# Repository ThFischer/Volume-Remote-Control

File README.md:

# Volume Remote Control

This project contains a hard- and software solution to control the volume, balance and muting of a stereo line signal.

## Motivation
I was not able to control the volume of my home cinema setup remotely, because I use a Logitech Z4 which has only a wired volume remote:
```
         Fire TV Stick
              ▼
HDMI to HDMI and Audio Converter
    ┌─────────┴────────────┐
    ▼                      ▼
Video Projector       2.1 Speaker System
                        (Logitech Z4)
```
## Hardware

The main components are a microcontroller ([ATmega328P](https://www.microchip.com/wwwproducts/en/ATmega328P)) and a electronic volume controller IC ([PT2257](https://dtsheet.com/doc/592434/ptc-pt2257-s)). You can find the KiCad files (schema and PCB) in the [hardware directory](./hardware/). I used a single layer PCB which I made via [direct toner transfer method](https://www.electronicshub.org/how-to-make-pcb-at-home/). The shape of the PCB fits exactly into a [TerraTec CINERGY T2 case](https://commons.wikimedia.org/wiki/File:TerraTec_Cinergy_T%C2%B2-92062.jpg). The Volume Remote Control is connected between the audio output of the HDMI Converter and audio input of the 2.1 Speaker System.

## Software
I used [Visual Studio Code](https://code.visualstudio.com/download) and the [PlatformIO extension](https://platformio.org/install/ide?install=vscode). You can find the PlatformIO project files in the [software directory](./software/). Thanks to ["IRMP - Infrared Multi Protocol Decoder + Encoder"](https://github.com/ukw100/IRMP) library it provides support for thousands of IR Remotes (I use a [Apple Remote 2nd Gen.](https://en.wikipedia.org/wiki/Apple_Remote)).

## Flashing the Firmware
I used an Arduino UNO to flash the ATmega328P via the ISP connector on the PCB. For more details see [ArduinoISP](https://www.arduino.cc/en/pmwiki.php?n=Tutorial/ArduinoISP)

## Handling

### "Learn a new remote" mode
The start of this mode is indicated by alternate green and red flashing LED until the first button is learned.

When the Controller is powered on without having learned successfully a remote before, it starts automatically in this mode. You can also enter this mode after a remote was already learned by power of and on the controller and press a button on the remote within the first 5 seconds (green LED is on).
Important: To prevent unintended re-learning (e.g. your remote stuck in the couch and a button is pressed permanently) a pressed button is ignored if this button and the first button to learn (Volume up) is the same!

It expects the learning of remote buttons in this order:

1. Volume up
1. Volume down
1. Mute on/off
1. Balance left
1. Balance right
1. Preset

Each successful learned button is confirmed by flashing the green LED for 1 second. If an invalid IR command was received (e.g. from a second remote which has a different address) the learning mode will be interrupted.
In case you don't want define all buttons (e.g. your remote has less buttons) you can press a button which was already assigned. In this case the function will be not supported.

If the last button is learned, the green LED flashes 3 times and the new learned buttons are stored into the non volatile memory of the µC. 

### Volume
Press the learned "Volume up" or "Volume down" button to increase or decrease the volume.

### Balance
Press the learned "Balance left" or "Balance right" button to shift the balance to the left or right.

### Mute
Press the learned "Mute" button to toggle mute on and off.

### Preset
To restore the presets for volume and balance press and release the learned "Preset" button.
To store the current volume and balance as presets press and hold the learned "Preset" button for 3 seconds.

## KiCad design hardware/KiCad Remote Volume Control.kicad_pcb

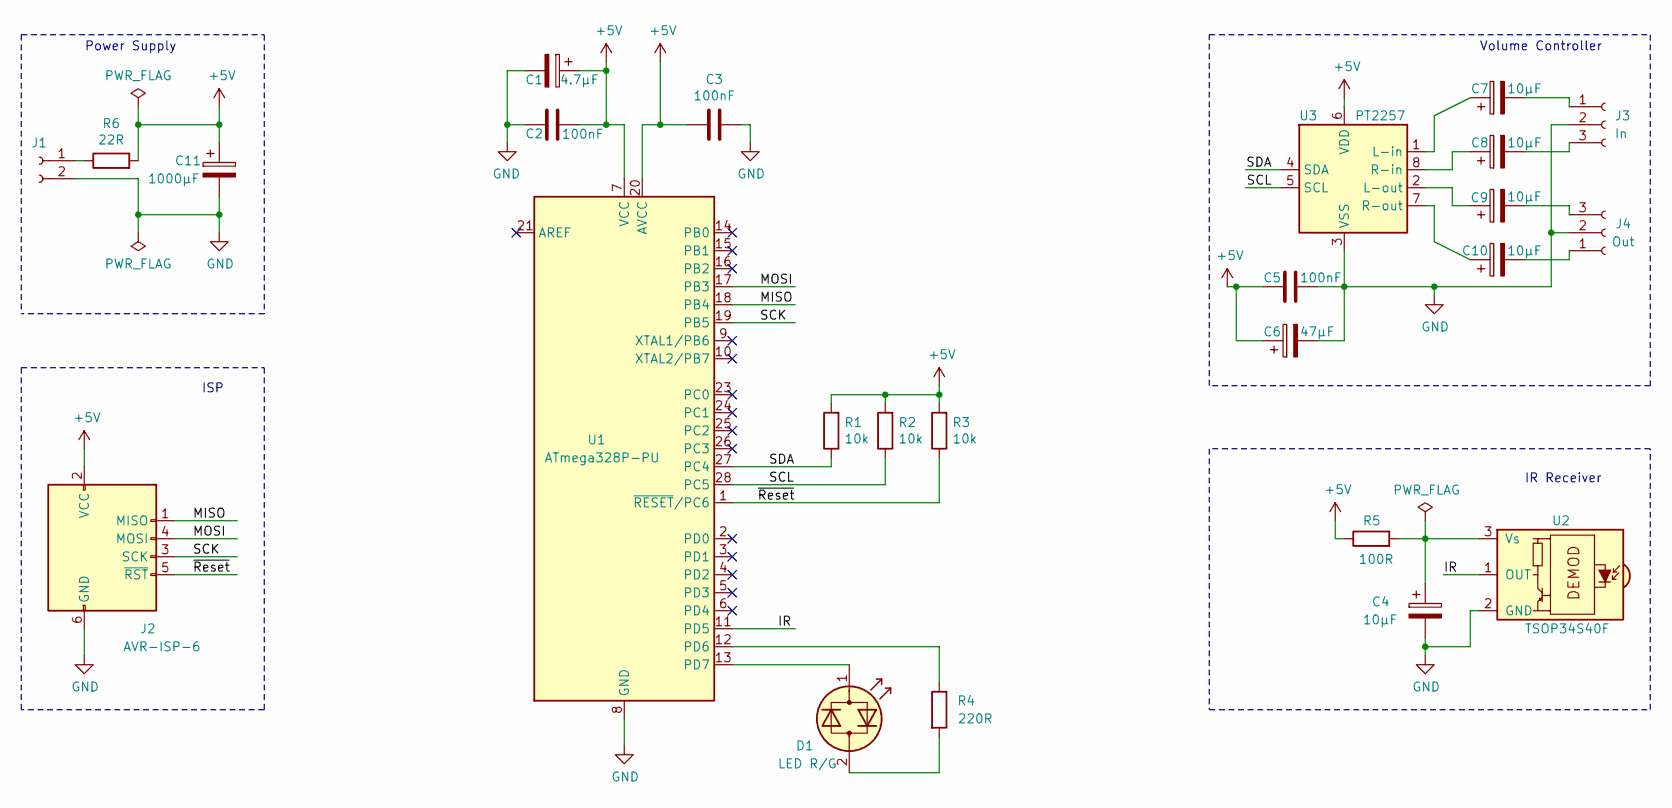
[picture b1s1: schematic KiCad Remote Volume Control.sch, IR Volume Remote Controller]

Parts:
C1: 4.7µF; CP_Radial_D4.0mm_P1.50mm
C2, C3, C5: 100nF; C_Disc_D3.0mm_W2.0mm_P2.50mm
C4, C7, C8, C9, C10: 10µF; CP_Radial_D4.0mm_P1.50mm
C6: 47µF; CP_Radial_D4.0mm_P1.50mm
C11: 1000µF; CP_Radial_D10.0mm_P5.00mm
D1: LED R/G; LED_D3.0mm
J1: Conn_01x02_Female; JST_XH_B2B-XH-A_1x02_P2.50mm_Vertical
J2: AVR-ISP-6; PinHeader_2x03_P2.54mm_Vertical
J3: In; PinHeader_1x03_P2.54mm_Vertical
J4: Out; PinHeader_1x03_P2.54mm_Vertical
R1, R2, R3: 10k; R_Axial_DIN0207_L6.3mm_D2.5mm_P2.54mm_Vertical
R4: 220R; R_Axial_DIN0207_L6.3mm_D2.5mm_P2.54mm_Vertical
R5: 100R; R_Axial_DIN0207_L6.3mm_D2.5mm_P2.54mm_Vertical
R6: 22R; R_Axial_DIN0207_L6.3mm_D2.5mm_P2.54mm_Vertical
U1: ATmega328P-PU; DIP-28_W7.62mm
U2: TSOP34S40F; Vishay_MOLD-3Pin
U3: PT2257; DIP-8_W7.62mm

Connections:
+5V: C1.1, C2.1, C3.1, C5.1, C6.1, C11.1, J2.2 (VCC), R1.2, R2.2, R3.2, R5.1, R6.2, U1.7 (VCC), U1.20 (AVCC), U3.6 (VDD)
/IR: U1.11 (PD5), U2.1 (OUT)
/MISO: J2.1 (MISO), U1.18 (PB4)
/MOSI: J2.4 (MOSI), U1.17 (PB3)
/SCK: J2.3 (SCK), U1.19 (PB5)
/SCL: R2.1, U1.28 (PC5), U3.5 (SCL)
/SDA: R1.1, U1.27 (PC4), U3.4 (SDA)
/~Reset: J2.5 (~RST), R3.1, U1.1 (~RESET~/PC6)
GND: C1.2, C2.2, C3.2, C4.2, C5.2, C6.2, C11.2, J1.2, J2.6 (GND), J3.2, J4.2, U1.8 (GND), U1.22 (GND), U2.2 (GND), U3.3 (VSS)
unnamed: C4.1, R5.2, U2.3 (Vs)
unnamed: C7.1, U3.1 (L-in)
unnamed: C7.2, J3.1
unnamed: C8.1, U3.8 (R-in)
unnamed: C8.2, J3.3
unnamed: C9.1, U3.2 (L-out)
unnamed: C9.2, J4.3
unnamed: C10.1, U3.7 (R-out)
unnamed: C10.2, J4.1
unnamed: D1.1 (KA), U1.13 (PD7)
unnamed: D1.2 (AK), R4.2
unnamed: J1.1, R6.1
unnamed: R4.1, U1.12 (PD6)

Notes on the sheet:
Power Supply
ISP
IR Receiver
Volume Controller

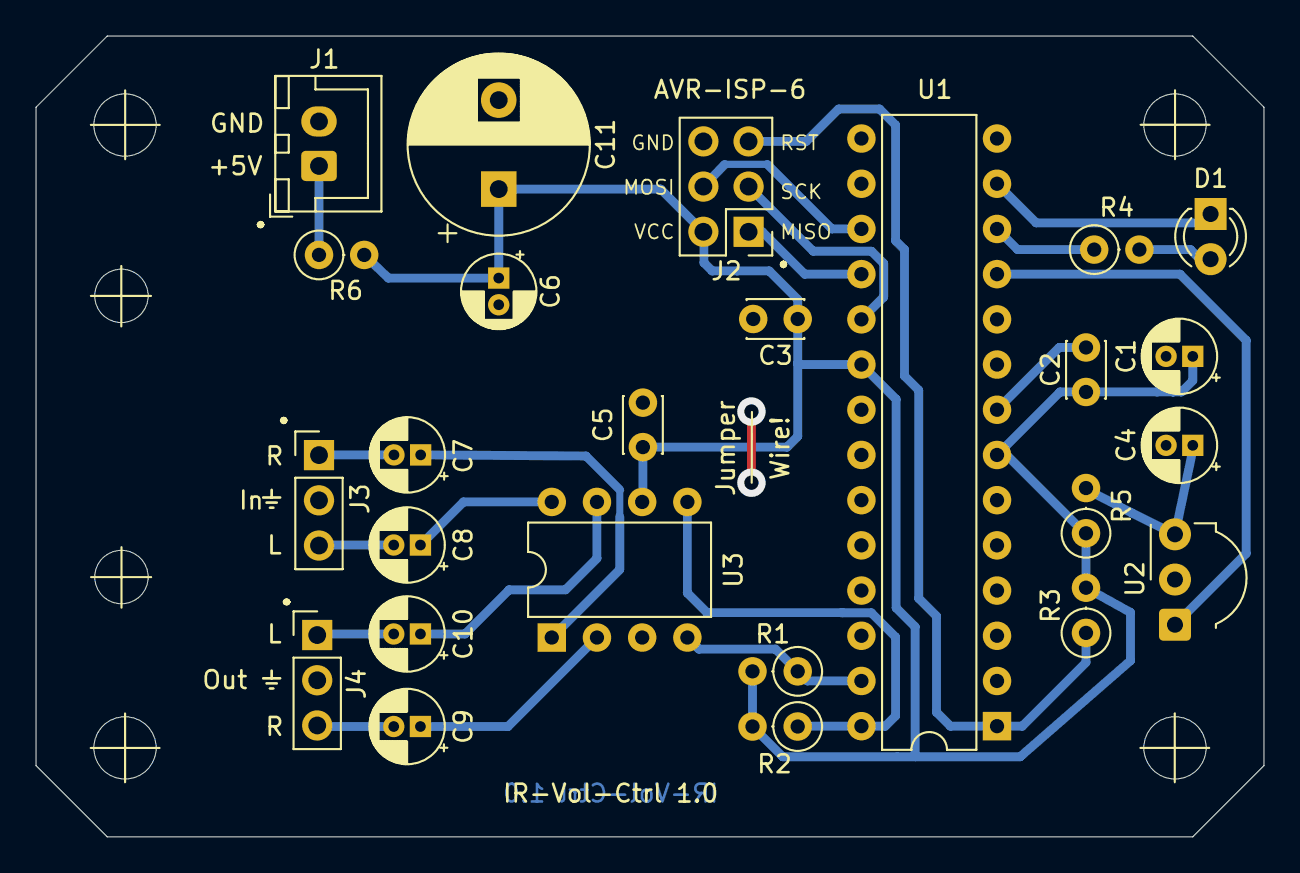
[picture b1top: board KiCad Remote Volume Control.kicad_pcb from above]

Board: 2 copper layers, 69.0 x 45.0 mm, 25 parts (0 on the bottom side), 22 nets.

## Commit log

2022-01-09 Make KiCad pathes relative
